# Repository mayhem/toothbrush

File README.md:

# toothbrush
Open source toothbrush.

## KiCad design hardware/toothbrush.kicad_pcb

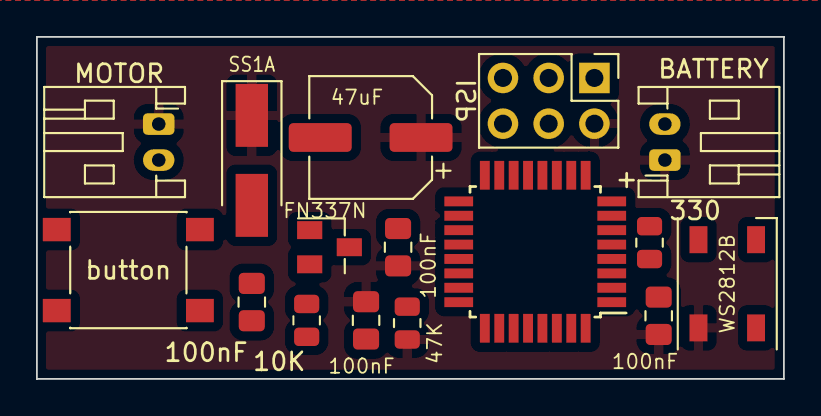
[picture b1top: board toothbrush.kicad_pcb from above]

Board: 2 copper layers, 41.5 x 19.0 mm, 16 parts (0 on the bottom side), 11 nets, no tracks yet.

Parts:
C1, C2, C3, C5: 100nF; C_0805_2012Metric_Pad1.18x1.45mm_HandSolder
C4: 47uF; CP_Elec_6.3x5.3
D1: SS1A; D_SMA_Handsoldering
D2: WS2812B; LED_WS2812B_PLCC4_5.0x5.0mm_P3.2mm
J2: ISP; PinHeader_2x03_P2.54mm_Vertical
J3: MOTOR; JST_PH_S2B-PH-K_1x02_P2.00mm_Horizontal
J4: BATTERY; JST_PH_S2B-PH-K_1x02_P2.00mm_Horizontal
Q1: FN337N; SuperSOT-3
R2: 10K; R_0805_2012Metric
R5: 330; R_0805_2012Metric
R6: 47K; R_0805_2012Metric
SW1: button; SW_Push_1P1T_NO_6x6mm_H9.5mm
U1: ATmega328P-A; TQFP-32_7x7mm_P0.8mm

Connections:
/BUTTON: SW1.1, U1.32 (PD2)
/FAN: C3.1, Q1.1 (B), R2.1, U1.13 (PB1)
/LED: R5.1, U1.1 (PD3)
/MISO: J2.1, U1.16 (PB4)
/MOSI: J2.4, U1.15 (PB3)
/RST: J2.5, R6.2, U1.29 (~RESET/PC6)
/SCK: J2.3, U1.17 (PB5)
/VCC: C1.1, C2.1, C4.1, C5.1, D1.1 (K), D2.1 (VDD), J2.2, J3.1, J4.1, R6.1, U1.4 (VCC), U1.6 (VCC), U1.18 (AVCC)
GND: C1.2, C2.2, C3.2, C5.2, D2.3 (VSS), J2.6, J4.2, Q1.3 (E), R2.2, SW1.2, U1.3 (GND), U1.5 (GND), U1.21 (GND)
unnamed: C4.2, D1.2 (A), J3.2, Q1.2 (C)
unnamed: D2.4 (DIN), R5.2

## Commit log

2022-12-14 First cut!
2022-12-14 Code template
2022-12-14 DOes the LED work?
2022-12-14 LED debugged and startup animation set
2022-12-14 Add motor support
2022-12-14 futz`
2022-12-20 It works!
2022-12-20 Setup timers, button interrupts
2022-12-20 Enable pull up resistor
2022-12-20 Cleanup
2022-12-20 Fix debounce
2022-12-20 Clock and ticks verified
2022-12-21 Switch debounce finally works
2022-12-21 Add sleep mode support
2022-12-21 Firmware is starting to shape up
2022-12-21 Sleep mode and power on/off working correctly now
2022-12-21 Start adding the time's up notification
2022-12-21 First cut of the firmware is done. sleeping, timer, everything.
2022-12-21 Turn power connector around to be more consistent with other things.

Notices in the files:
hardware/toothbrush.kicad_pcb:
(c) 2022 Mayhem & Chaos
